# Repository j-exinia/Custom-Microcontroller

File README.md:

# Microcontroller Breakout Board

## Block Diagram

## Peripherals 

### Microprocessor 

* [ARM Cortex M0+](https://www.mouser.com/datasheet/2/389/dm00613881-1799439.pdf)

### USB Mini Port

* [UJ2-MBH](https://www.mouser.com/datasheet/2/670/uj2-mbh-smt-1313286.pdf)

### USB to UART

* [FT230XS-R](https://www.mouser.com/datasheet/2/163/DS_FT230X-5395.pdf)

### Voltage Regulator

* [TPS77733DR](http://www.ti.com/lit/ds/symlink/tps777.pdf)

## Images
, 

## Designers

* **Jorge Exinia** - *PCB design* - [j-exinia](https://github.com/j-exinia)

### Built With

* [KiCad](https://kicad-pcb.org/) - The PCB design software used

### Errata

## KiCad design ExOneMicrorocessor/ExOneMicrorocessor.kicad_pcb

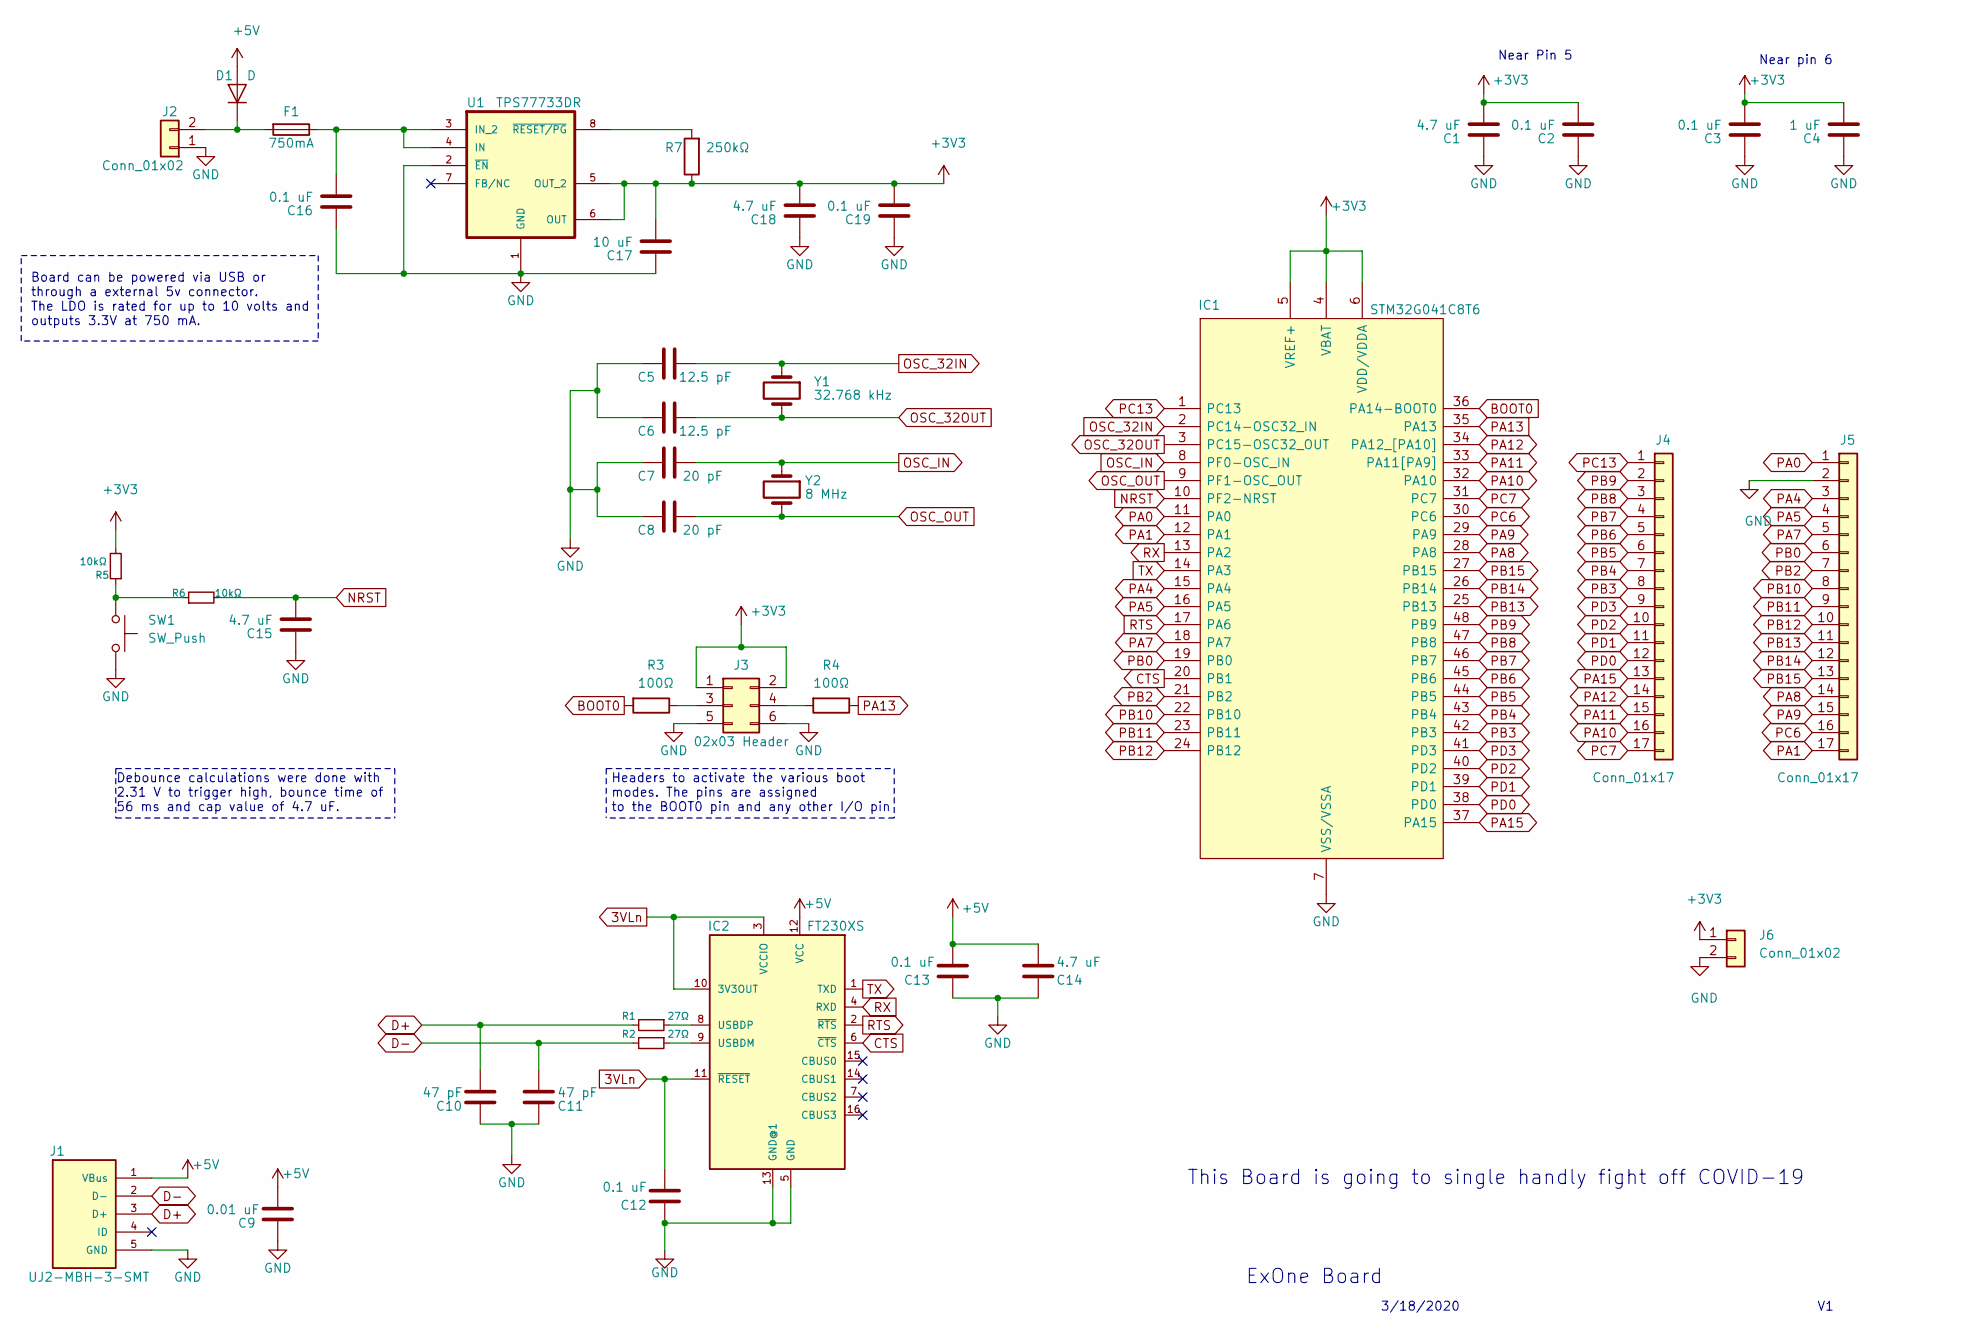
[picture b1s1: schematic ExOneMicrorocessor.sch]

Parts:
C1, C14, C15, C18: 4.7 uF; C_0603_1608Metric_Pad1.05x0.95mm_HandSolder
C2, C3, C12, C13, C16, C19: 0.1 uF; C_0603_1608Metric_Pad1.05x0.95mm_HandSolder
C4: 1 uF; C_0603_1608Metric_Pad1.05x0.95mm_HandSolder
C5, C6: 12.5 pF; C_0603_1608Metric_Pad1.05x0.95mm_HandSolder
C7, C8: 20 pF; C_0603_1608Metric_Pad1.05x0.95mm_HandSolder
C9: 0.01 uF; C_0603_1608Metric_Pad1.05x0.95mm_HandSolder
C10, C11: 47 pF; C_0603_1608Metric_Pad1.05x0.95mm_HandSolder
C17: 10 uF; C_0603_1608Metric_Pad1.05x0.95mm_HandSolder
D1: D; D_SOD-123
F1: 750mA; Fuse_1206_3216Metric_Pad1.42x1.75mm_HandSolder
IC1: STM32G041C8T6; STM32G041C8; Mouser Part Number 511-STM32G041C8T6
IC2: FT230XS
J1: UJ2-MBH-3-SMT; UJ2-MBH-SMT
J2: Conn_01x02; JST_EH_B2B-EH-A_1x02_P2.50mm_Vertical
J3: 02x03 Header; PinHeader_2x03_P2.54mm_Vertical
J4, J5: Conn_01x17; PinHeader_1x17_P2.54mm_Vertical
J6: Conn_01x02; PinHeader_1x02_P2.54mm_Vertical
R1, R2: 27Ω; R_0603_1608Metric_Pad1.05x0.95mm_HandSolder
R3, R4: 100Ω; R_0603_1608Metric_Pad1.05x0.95mm_HandSolder
R5, R6: 10kΩ; R_0603_1608Metric_Pad1.05x0.95mm_HandSolder
R7: 250kΩ; R_0603_1608Metric_Pad1.05x0.95mm_HandSolder
SW1: SW_Push; PTS636SM25SMTRLFS
U1: TPS77733DR; TPS77733
Y1: 32.768 kHz; Crystal_SMD_3215-2Pin_3.2x1.5mm
Y2: 8 MHz; Crystal_SMD_HC49-SD_HandSoldering

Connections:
3VLn: C12.1, IC2.3 (VCCIO), IC2.10 (3V3OUT), IC2.11 (~RESET~)
+3V3: C1.2, C2.2, C3.2, C4.2, C17.2, C18.2, C19.2, IC1.4 (VBAT), IC1.5 (VREF+), IC1.6 (VDD/VDDA), J3.1, J3.2, J6.1, R5.2, R7.1, U1.5 (OUT_2), U1.6 (OUT)
+5V: C9.1, C13.1, C14.2, D1.2 (A), IC2.12 (VCC), J1.1 (VBus)
BOOT0: IC1.36 (PA14-BOOT0), R3.2
CTS: IC1.20 (PB1), IC2.6 (~CTS~)
D+: C10.1, J1.3 (D+), R1.2
D-: C11.1, J1.2 (D-), R2.2
GND: C1.1, C2.1, C3.1, C4.1, C5.1, C6.1, C7.1, C8.1, C9.2, C10.2, C11.2, C12.2, C13.2, C14.1, C15.1, C16.1, C17.1, C18.1, C19.1, IC1.7 (VSS/VSSA), IC2.5 (GND), IC2.13 (GND@1), J1.5 (GND), J2.1, J3.5, J3.6, J5.2, J6.2, SW1.2, U1.1 (GND), U1.2 (~EN)
NRST: C15.2, IC1.10 (PF2-NRST), R6.2
unnamed: C16.2, F1.1, U1.3 (IN_2), U1.4 (IN)
unnamed: D1.1 (K), F1.2, J2.2
unnamed: IC2.8 (USBDP), R1.1
unnamed: IC2.9 (USBDM), R2.1
unnamed: J3.3, R3.1
unnamed: J3.4, R4.2
unnamed: R5.1, R6.1, SW1.1
unnamed: R7.2, U1.8 (~RESET/PG)
OSC_32IN: C5.2, IC1.2 (PC14-OSC32_IN), Y1.1
OSC_32OUT: C6.2, IC1.3 (PC15-OSC32_OUT), Y1.2
OSC_IN: C7.2, IC1.8 (PF0-OSC_IN), Y2.1
OSC_OUT: C8.2, IC1.9 (PF1-OSC_OUT), Y2.2
PA0: IC1.11 (PA0), J5.1
PA1: IC1.12 (PA1), J5.17
PA4: IC1.15 (PA4), J5.3
PA5: IC1.16 (PA5), J5.4
PA7: IC1.18 (PA7), J5.5
PA8: IC1.28 (PA8), J5.14
PA9: IC1.29 (PA9), J5.15
PA10: IC1.32 (PA10), J4.16
PA11: IC1.33 (PA11[PA9]), J4.15
PA12: IC1.34 (PA12_[PA10]), J4.14
PA13: IC1.35 (PA13), R4.1
PA15: IC1.37 (PA15), J4.13
PB0: IC1.19 (PB0), J5.6
PB2: IC1.21 (PB2), J5.7
PB3: IC1.42 (PB3), J4.8
PB4: IC1.43 (PB4), J4.7
PB5: IC1.44 (PB5), J4.6
PB6: IC1.45 (PB6), J4.5
PB7: IC1.46 (PB7), J4.4
PB8: IC1.47 (PB8), J4.3
PB9: IC1.48 (PB9), J4.2
PB10: IC1.22 (PB10), J5.8
PB11: IC1.23 (PB11), J5.9
PB12: IC1.24 (PB12), J5.10
PB13: IC1.25 (PB13), J5.11
PB14: IC1.26 (PB14), J5.12
PB15: IC1.27 (PB15), J5.13
PC6: IC1.30 (PC6), J5.16
PC7: IC1.31 (PC7), J4.17
PC13: IC1.1 (PC13), J4.1
PD0: IC1.38 (PD0), J4.12
PD1: IC1.39 (PD1), J4.11
PD2: IC1.40 (PD2), J4.10
PD3: IC1.41 (PD3), J4.9
RTS: IC1.17 (PA6), IC2.2 (~RTS~)
RX: IC1.13 (PA2), IC2.4 (RXD)
TX: IC1.14 (PA3), IC2.1 (TXD)

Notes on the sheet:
3/18/2020
This Board is going to single handly fight off COVID-19
ExOne Board
Near Pin 5
Near pin 6
Debounce calculations were done with 2.31 V to trigger high, bounce time of 56 ms and cap value of 4.7 uF.
Board can be powered via USB or through a external 5v connector. The LDO is rated for up to 10 volts and outputs 3.3V at 750 mA.
Headers to activate the various boot modes. The pins are assigned to the BOOT0 pin and any other I/O pin

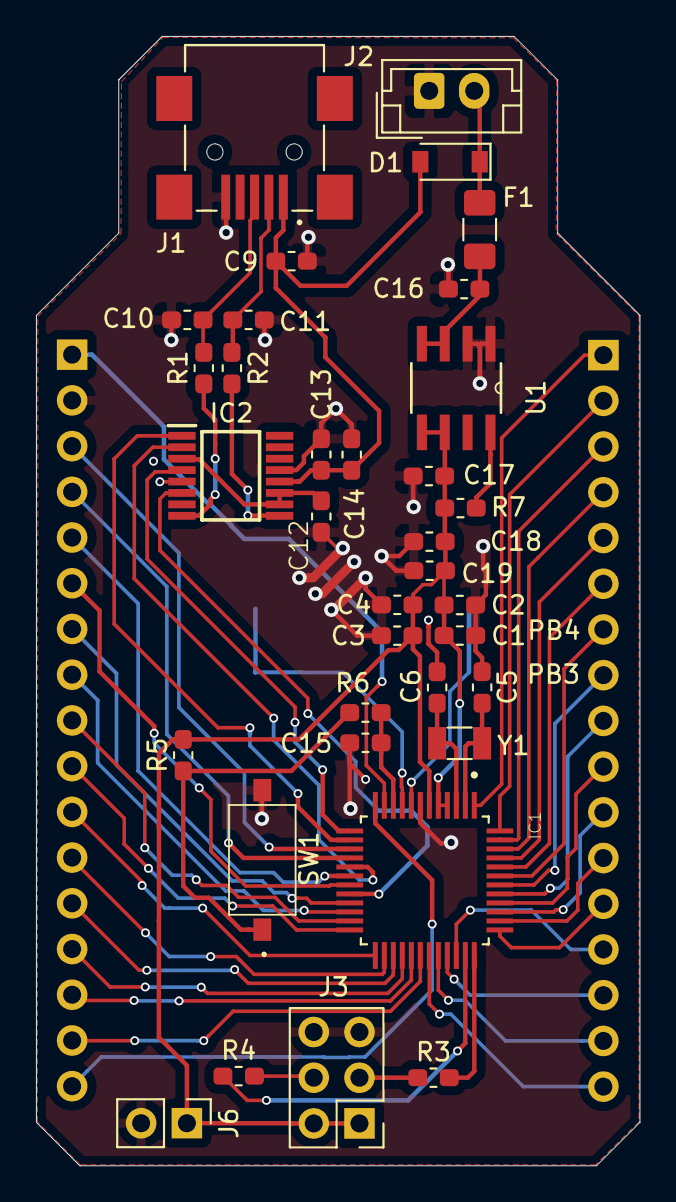
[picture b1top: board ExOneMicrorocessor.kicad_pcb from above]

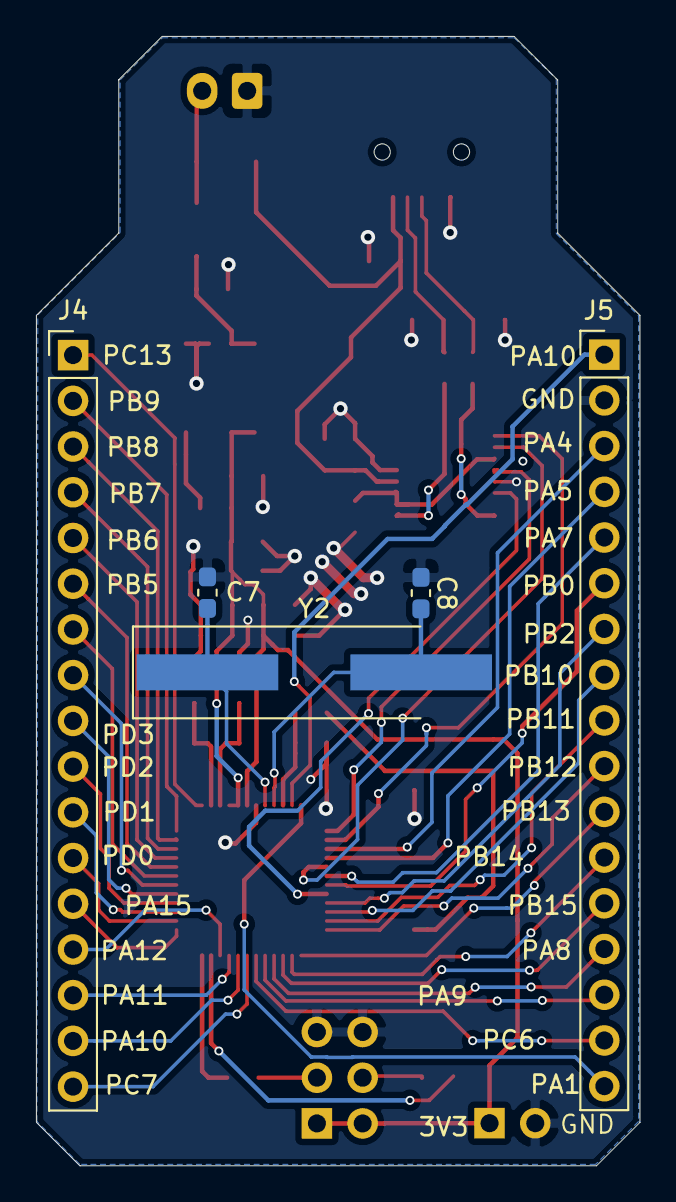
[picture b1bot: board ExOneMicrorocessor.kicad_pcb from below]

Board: 2 copper layers, 33.5 x 62.7 mm, 40 parts (5 on the bottom side), 58 nets.

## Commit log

2020-03-17 Added an images folder with an immage
2020-03-18 Added library folder with library for parts
2020-03-18 Started work on schematic
2020-03-18 finished the schematic for the microP
2020-03-18 nvm fixed some directions on some pins
2020-03-19 Updated Schematic
    Updated net names
    Added various notes explaning the design further
    Changed the LDO IC
2020-03-19 Just forgot to save it in the schema
2020-03-19 Fixed schematic
    Change bypass caps on the IC
    added pull up resistors on the switch
    removed some comments
2020-03-20 started work on the PCB layout
2020-03-22 started PCB LAyout
2020-03-24 Added Photos of the PCB
2020-03-24 FInished work on pcb , added some pads for 3v3 and gnd
2020-03-24 Added Gerber files and drill files
2020-03-30 Added IRL pics
2020-08-12 push for T
2020-08-12 made prod files JLC complimant
2020-08-12 JLC files
